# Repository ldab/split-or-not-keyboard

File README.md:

# split-or-not-keyboard

FoMO ZMK Ortholinear keyboard, if you can't decide between split or not.

## Todo

## Note

- Polling mode add extra 60uA
-

## Why?

Maybe you are here because you are considering a ZMK keyboard and you don't know if you are ready for a split keyboard? Or you don't know if you prefer a rectangular or "ergo" design? Or you have fear or missing out and want to try all of them but don't want to spend all your money?

## How?

## Designed with KiCAD 7.09

- Important libs are added as plugin as per described on https://github.com/ebastler/marbastlib

## BOM

* 1x Seeed Studio XIAO nRF52840
* 1x PCA9555 GPIO Expander
* 60x 1N4148W diodes
* 60x Kailh choc switches
* 60x Kailh choc keycap
* 60x Kailh choc Hotswap Sockets

## Variants

### Basic60

### Ergo56

## Battery life

## Outro

- Some similarities with below may be found:
  - https://github.com/piit79/rev57lp/

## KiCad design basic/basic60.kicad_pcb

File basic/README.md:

# split-or-not-keyboard
FoMO ZMK Ortholinear keyboard, if you can't decide between split or not.

## Todo

## Why?

Maybe you are here because you are considering a ZMK keyboard and you don't know if you are ready for a split keyboard? Or you don't know if you prefer a rectangular or "ergo" design? Or you have fear or missing out and want to try all of them but don't want to spend all your money?

## How?

## Designed with KiCAD 7.09

* Important libs are added as plugin as per described on https://github.com/ebastler/marbastlib

## Outro

* Some similarities with below may be found:
  * https://github.com/piit79/rev57lp/
  * https://github.com/MakotoKurauchi/helix

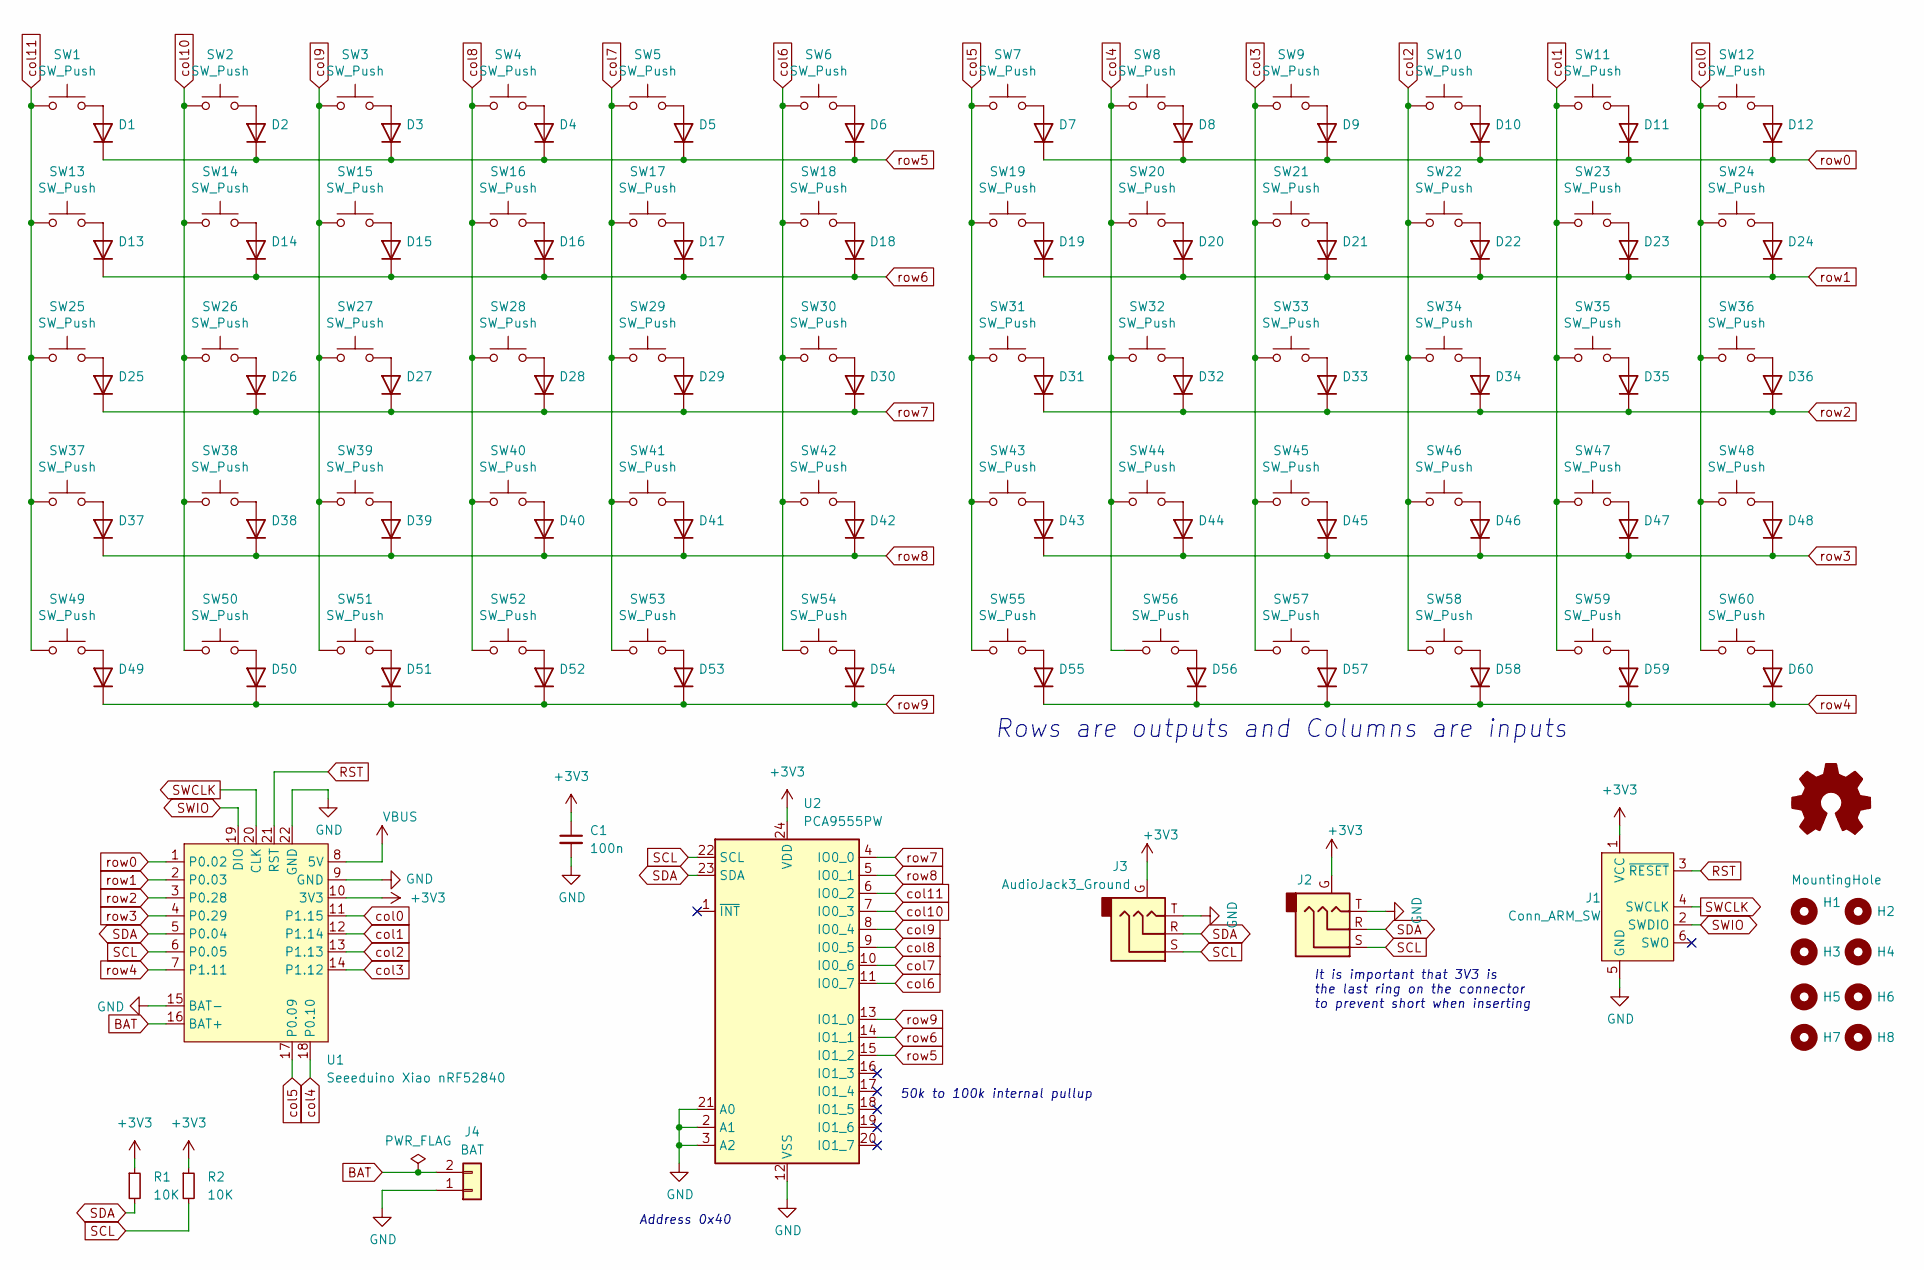
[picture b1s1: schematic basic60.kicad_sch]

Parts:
C1: 100n; C_0603_1608Metric_Pad1.08x0.95mm_HandSolder
D1, D2, D3, D4, D5, D6, D7, D8, D9, D10, D11, D12, D13, D14, D15, D16, D17, D18, D19, D20, D21, D22, D23, D24, D25, D26, D27, D28, D29, D30, D31, D32, D33, D34, D35, D36, D37, D38, D39, D40, D41, D42, D43, D44, D45, D46, D47, D48, D49, D50, D51, D52, D53, D54, D55, D56, D57, D58, D59, D60: D_SOD-123
H1, H2, H3, H4, H5, H6, H7, H8: MountingHole; MountingHole_3.5mm
J1: Conn_ARM_SW; PinHeader_2x05_P1.27mm_Vertical_SMD
J2, J3: AudioJack3_Ground; Jack_3.5mm_PJ320D_Horizontal
J4: BAT; JST_PH_S2B-PH-SM4-TB_1x02-1MP_P2.00mm_Horizontal
R1, R2: 10K; R_0603_1608Metric_Pad0.98x0.95mm_HandSolder
SW1, SW2, SW3, SW4, SW5, SW6, SW7, SW8, SW9, SW10, SW11, SW12, SW13, SW14, SW15, SW16, SW17, SW18, SW19, SW20, SW21, SW22, SW23, SW24, SW25, SW26, SW27, SW28, SW29, SW30, SW31, SW32, SW33, SW34, SW35, SW36, SW37, SW38, SW39, SW40, SW41, SW42, SW43, SW44, SW45, SW46, SW47, SW48, SW49, SW50, SW51, SW52, SW53, SW54, SW55, SW56, SW57, SW58, SW59, SW60: SW_Push; SW_choc_v1_HS_1u
U1: Seeeduino Xiao nRF52840; Xiao_nRF52840_AC_Reflow
U2: PCA9555PW; TSSOP-24_4.4x7.8mm_P0.65mm

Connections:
+3V3: C1.1, J1.1 (VCC), J2.G, J3.G, R1.1, R2.1, U1.10 (3V3), U2.24 (VDD)
BAT: J4.2, U1.16 (BAT+)
GND: C1.2, J1.5 (GND), J2.T, J3.T, J4.1, U1.9 (GND), U1.15 (BAT-), U1.22 (GND), U2.2 (A1), U2.3 (A2), U2.12 (VSS), U2.21 (A0)
unnamed: D1.2 (A), SW1.2
unnamed: D2.2 (A), SW2.2
unnamed: D3.2 (A), SW3.2
unnamed: D4.2 (A), SW4.2
unnamed: D5.2 (A), SW5.2
unnamed: D6.2 (A), SW6.2
unnamed: D7.2 (A), SW7.2
unnamed: D8.2 (A), SW8.2
unnamed: D9.2 (A), SW9.2
unnamed: D10.2 (A), SW10.2
unnamed: D11.2 (A), SW11.2
unnamed: D12.2 (A), SW12.2
unnamed: D13.2 (A), SW13.2
unnamed: D14.2 (A), SW14.2
unnamed: D15.2 (A), SW15.2
unnamed: D16.2 (A), SW16.2
unnamed: D17.2 (A), SW17.2
unnamed: D18.2 (A), SW18.2
unnamed: D19.2 (A), SW19.2
unnamed: D20.2 (A), SW20.2
unnamed: D21.2 (A), SW21.2
unnamed: D22.2 (A), SW22.2
unnamed: D23.2 (A), SW23.2
unnamed: D24.2 (A), SW24.2
unnamed: D25.2 (A), SW25.2
unnamed: D26.2 (A), SW26.2
unnamed: D27.2 (A), SW27.2
unnamed: D28.2 (A), SW28.2
unnamed: D29.2 (A), SW29.2
unnamed: D30.2 (A), SW30.2
unnamed: D31.2 (A), SW31.2
unnamed: D32.2 (A), SW32.2
unnamed: D33.2 (A), SW33.2
unnamed: D34.2 (A), SW34.2
unnamed: D35.2 (A), SW35.2
unnamed: D36.2 (A), SW36.2
unnamed: D37.2 (A), SW37.2
unnamed: D38.2 (A), SW38.2
unnamed: D39.2 (A), SW39.2
unnamed: D40.2 (A), SW40.2
unnamed: D41.2 (A), SW41.2
unnamed: D42.2 (A), SW42.2
unnamed: D43.2 (A), SW43.2
unnamed: D44.2 (A), SW44.2
unnamed: D45.2 (A), SW45.2
unnamed: D46.2 (A), SW46.2
unnamed: D47.2 (A), SW47.2
unnamed: D48.2 (A), SW48.2
unnamed: D49.2 (A), SW49.2
unnamed: D50.2 (A), SW50.2
unnamed: D51.2 (A), SW51.2
unnamed: D52.2 (A), SW52.2
unnamed: D53.2 (A), SW53.2
unnamed: D54.2 (A), SW54.2
unnamed: D55.2 (A), SW55.2
unnamed: D56.2 (A), SW56.2
unnamed: D57.2 (A), SW57.2
unnamed: D58.2 (A), SW58.2
unnamed: D59.2 (A), SW59.2
unnamed: D60.2 (A), SW60.2
RST: J1.3 (~RESET), U1.21 (RST)
SCL: J2.S, J3.S, R2.2, U1.6 (P0.05), U2.22 (SCL)
SDA: J2.R, J3.R, R1.2, U1.5 (P0.04), U2.23 (SDA)
SWCLK: J1.4 (SWCLK), U1.20 (CLK)
SWIO: J1.2 (SWDIO), U1.19 (DIO)
VBUS: U1.8 (5V)
col0: SW12.1, SW24.1, SW36.1, SW48.1, SW60.1, U1.11 (P1.15)
col1: SW11.1, SW23.1, SW35.1, SW47.1, SW59.1, U1.12 (P1.14)
col2: SW10.1, SW22.1, SW34.1, SW46.1, SW58.1, U1.13 (P1.13)
col3: SW9.1, SW21.1, SW33.1, SW45.1, SW57.1, U1.14 (P1.12)
col4: SW8.1, SW20.1, SW32.1, SW44.1, SW56.1, U1.18 (P0.10)
col5: SW7.1, SW19.1, SW31.1, SW43.1, SW55.1, U1.17 (P0.09)
col6: SW6.1, SW18.1, SW30.1, SW42.1, SW54.1, U2.11 (IO0_7)
col7: SW5.1, SW17.1, SW29.1, SW41.1, SW53.1, U2.10 (IO0_6)
col8: SW4.1, SW16.1, SW28.1, SW40.1, SW52.1, U2.9 (IO0_5)
col9: SW3.1, SW15.1, SW27.1, SW39.1, SW51.1, U2.8 (IO0_4)
col10: SW2.1, SW14.1, SW26.1, SW38.1, SW50.1, U2.7 (IO0_3)
col11: SW1.1, SW13.1, SW25.1, SW37.1, SW49.1, U2.6 (IO0_2)
row0: D7.1 (K), D8.1 (K), D9.1 (K), D10.1 (K), D11.1 (K), D12.1 (K), U1.1 (P0.02)
row1: D19.1 (K), D20.1 (K), D21.1 (K), D22.1 (K), D23.1 (K), D24.1 (K), U1.2 (P0.03)
row2: D31.1 (K), D32.1 (K), D33.1 (K), D34.1 (K), D35.1 (K), D36.1 (K), U1.3 (P0.28)
row3: D43.1 (K), D44.1 (K), D45.1 (K), D46.1 (K), D47.1 (K), D48.1 (K), U1.4 (P0.29)
row4: D55.1 (K), D56.1 (K), D57.1 (K), D58.1 (K), D59.1 (K), D60.1 (K), U1.7 (P1.11)
row5: D1.1 (K), D2.1 (K), D3.1 (K), D4.1 (K), D5.1 (K), D6.1 (K), U2.15 (IO1_2)
row6: D13.1 (K), D14.1 (K), D15.1 (K), D16.1 (K), D17.1 (K), D18.1 (K), U2.14 (IO1_1)
row7: D25.1 (K), D26.1 (K), D27.1 (K), D28.1 (K), D29.1 (K), D30.1 (K), U2.4 (IO0_0)
row8: D37.1 (K), D38.1 (K), D39.1 (K), D40.1 (K), D41.1 (K), D42.1 (K), U2.5 (IO0_1)
row9: D49.1 (K), D50.1 (K), D51.1 (K), D52.1 (K), D53.1 (K), D54.1 (K), U2.13 (IO1_0)

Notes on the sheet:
It is important that 3V3 is the last ring on the connector to prevent short when inserting
Address 0x40
50k to 100k internal pullup
Rows are outputs and Columns are inputs

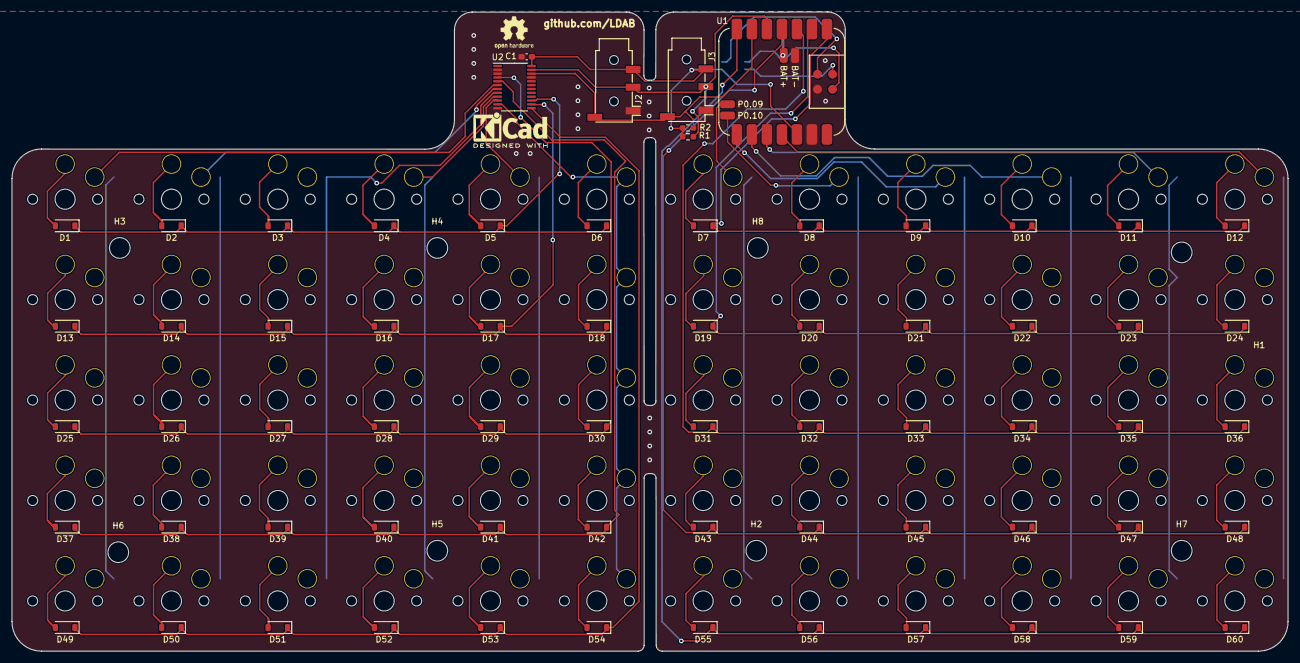
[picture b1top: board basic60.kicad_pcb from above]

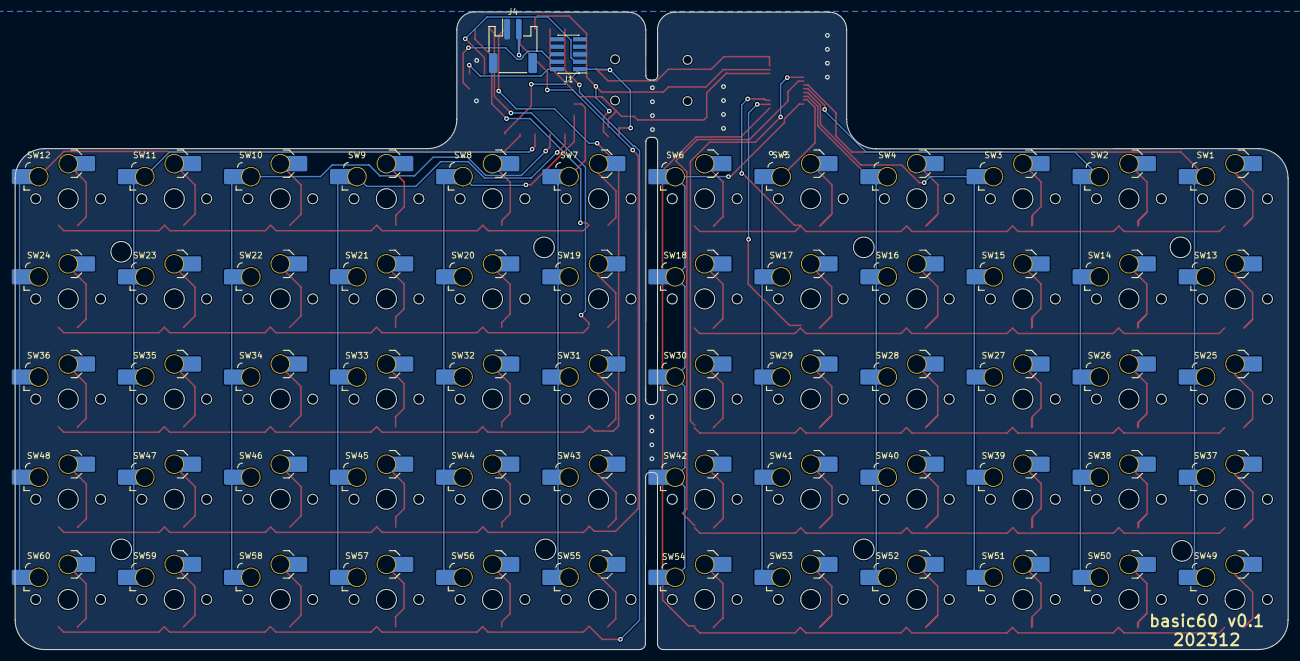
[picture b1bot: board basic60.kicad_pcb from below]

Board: 2 copper layers, 215.9 x 108.1 mm, 137 parts (62 on the bottom side), 90 nets.

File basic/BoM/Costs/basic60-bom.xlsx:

|  | KiBot Bill of Materials
 |  | Schematic: | basic60 | Component Groups: | 7
 |  | Variant: | default | Component Count: | 127 (127 SMD/ 0 THT)
 |  | Revision: | 0.1 | Fitted Components: | 127 (127 SMD/ 0 THT)
 |  | Date: | 2023-12-20 | Number of PCBs: | 1
 |  | KiCad Version: | 7.0.9-7.0.9~ubuntu22.04.1 | Total Components: | 127
Row | Description | Part | References | Value | Footprint | Quantity Per PCB | Status | Datasheet | Sim.Device | Sim.Pins | Sim.Enable
1 | Unpolarized capacitor, small symbol | C_Small | C1 | 100n | C_0603_1608Metric_Pad1.08x0.95mm_HandSolder | 1 |  | ~
2 | 75V 0.15A Fast Switching Diode, SOD-123 | 1N4148W | D1 D2 D3 D4 D5 D6 D7 D8 D9 D10 D11 D12 D13 D14 D15 D16 D17 D18 D19 D20 D21 D22 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 | ~ | D_SOD-123 | 60 |  | https://www.vishay.com/docs/85748/1n4148w.pdf | D | 1=K 2=A
3 | Audio Jack, 3 Poles (Stereo / TRS), Grounded Sleeve | AudioJack3_Ground | J2 J3 | AudioJack3_Ground | Jack_3.5mm_PJ320D_Horizontal | 2 |  | ~
4 | Generic connector, single row, 01x02, script generated (kicad-library-utils/sch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 | Conn_01x02 | J4 | BAT | JST_PH_S2B-PH-SM4-TB_1x02-1MP_P2.00mm_Horizontal | 1 |  | ~
5 | Resistor, small symbol | R_Small | R1 R2 | 10K | R_0603_1608Metric_Pad0.98x0.95mm_HandSolder | 2 |  | ~
6 | Push button switch, generic, two pins | SW_Push | SW1 SW2 SW3 SW4 SW5 SW6 SW7 SW8 SW9 SW10 SW11 SW12 SW13 SW14 SW15 SW16 SW17 SW1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 | SW_Push | SW_choc_v1_HS_1u | 60 |  | ~
7 | IO expander 16 GPIO, I2C 400kHz, Interrupt, 2.3 - 5.5V, TSSOP-24 | PCA9555PW | U2 | PCA9555PW | TSSOP-24_4.4x7.8mm_P0.65mm | 1 |  | https://www.nxp.com/docs/en/data-sheet/PCA9555.pdf

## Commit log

2023-12-20 start somewhere
2023-12-20 schematic done, ERC pass
2023-12-20 all today
2023-12-20 do less
2023-12-21 stage
2023-12-21 add some files
2023-12-21 finish pcb
2023-12-21 basic60
2023-12-21 kibot
2023-12-30 add zephyr fw for basic60
2023-12-30 Wergo56 init zmk
2024-01-03 Wkeymap for basic
2024-01-03 ergo keymap
2024-01-04 fix minor pcb stuff
2024-01-14 move pipe key
2024-01-20 short sleep
2025-04-24 upload CI tools
2025-04-24 Revert "short sleep"
    This reverts commit a65dfa24fa4d67b4ab809a6d76214c46cc9e7593.
2025-04-24 solve warnings
2025-04-24 good now
2025-04-24 Pooling FW
2026-01-26 Update board configuration in build.yaml to use 'xiao_ble'

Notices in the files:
README.md:
License: WTFPL
